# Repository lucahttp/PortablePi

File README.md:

# Portable Pi

Is a Father Board witch can connect to the raspberry pi (currently compatible to this gpio configuration, orange pi thinkercard, an anothers) this aport an Screen and keyboard (on one board) then i will add more things like audio jack, ethernet port, hub USB and everything you can imagine and put in your pockets.

render of prototype ver 8.8

## History
it started when i wanted to buy the newly released Pocket Chip (https://imgur.com/l437LvK 50 USD + taxes + shipping, something of 120 USD)the chip is a competitor of the raspberry pi but offered for 9 USD and for 40 USD more could you make this pocket.

everything looked like fine until the company that makes CHIP, declared bankrupt.

 # Search a compatible keyboard for the portable pi

 ## 1. Usb Bluetooth keyboard (cheaply)
 
the first option I thought (my father told me) was a bluetooth keyboard (is very cheaply opcion for those dont like the hardware) but i think isnt practical

 ## 2. Xbox ChatPad
 
the second opcion is a Xbox Chatpad but is missing keys like >< ,Ctrl , Alt, Command and others.
if you not need this keys is a good opcion for this project

the way to connect to the raspberry is a reprogram the Microchip PIC inside the keyboard, BenHacksShow show how do it [here](https://www.youtube.com/watch?v=Hjdj14C_jAI) and others examples [with raspberry](https://www.youtube.com/watch?v=2sVS-jMGD7w), [an brazilian](https://www.youtube.com/watch?v=Mo7BqMrNIDs) and [this](https://www.youtube.com/watch?v=I20lXAS_IJs)

it also can use directly like TX/RX but have to run aprogram to convert this signals in keyboard inputs and it slow down the limited resources of the computer. [here in reddit](https://www.reddit.com/r/raspberry_pi/comments/5t4xgy/raspberry_pi_xbox_chatpad_keyboard/)

 ## 3. Arduino Usb Keyboard or Serial 
 
the third opcion that came my way that i was found are a Arduino Pro Micro as a USB keyboard like [teensy Thumb Keyboard](https://hackaday.io/project/162281-teensy-thumb-keyboard) but in this opcion i would have to conect via USB to the raspberry and this is not a good idea because isnt practical

but i dont discard the idea of adapt this opcion for use via GPIO

- the teensy Thumb Keyboard
  [teensy Thumb Keyboard](https://hackaday.io/project/162281-teensy-thumb-keyboard) 

 - RC2014 keyboard
 
   The RC2014 [page](http://rc2014.co.uk/modules/universal-micro-keyboard/) shown a project but i dont have any idea of how to       
   adapt this to PortablePi

   [Uinput: The New Hope]()
 ## 4. Usb keyboard (very cheaply)
 
 This opcion is better for those do not have a way to get electronic components but the layout and matrix config is not prepared to direct access in the keyboard but could be config these features via software

 [design of cheaply USB Keyboard opcion](https://github.com/lukaneco/USB-keyboard-Board-PCB-pinout-diagram)

 ## 5. the way most factible is TCA8418

I found that they use the other projects like PocketChip or qwertyPi and others better keyboards for raspberry pi (and others microcomputers) more professionals. the problem is that component isnt easyly to found in my country and is a smaller than otrer solutions (hard to solder to the board).

a good news is that the documentation in the [manufacturer page](http://www.ti.com/product/TCA8418)

https://e2e.ti.com/support/interface/f/138/t/202938

[Datasheet of TCA8418](www.ti.com/lit/ds/symlink/tca8418.pdf)

[Code for malti](https://hackaday.io/project/5081-malti/log/17068-it-lives)

- [Malti](https://hackaday.io/project/5081-malti) is a similar project but that dont have the idea of easy plug and play.

- [qwertyPi](https://mozzwald.com/articles/2017/12/01/qwertypi-a-handheld-raspberry-pi-qwerty-computer) is the more similar  project but that dont have the easy plug of the raspberry 

- [Ben Heck’s DIY Calculator](https://www.youtube.com/watch?v=lJu1ij_Emlk) is a similar project for other destiny

- [other font of information]() that guy have an project to make this way (the page is writed in german)

  - [video](https://www.youtube.com/watch?v=j4ymw0hWN1o)
  
  - [web page](https://5volt-junkie.net/i2c-keypad/)
  
- [pwav robot](https://twitter.com/pwavrobot) is other guy that make something with TCA8418

  - [link](https://twitter.com/pwavrobot/status/1075758165944385536)

  - [snaponair](http://www.snaponair.com/)

  - [lorawan pager](https://hackaday.io/project/22038-the-lorawan-pager)

  - [zerophone](https://hackaday.io/project/19035-zerophone-a-raspberry-pi-smartphone)

repeat, the problem is the shipping from US or China is very expensive and it takes a long time to get here.
i found an options to buy in [Aliexpress](https://es.aliexpress.com/wholesale?catId=0&initiative_id=SB_20190210085412&SearchText=TCA8418) relatively cheap, Mouser, TI store and others sellers the shipping cost is more than aliexpress but more quickly (about 40 usd the shipping cost).

 ## 6. the way most cheaply and elaborate is PCF8574 with Python
 ### 12/03/19
I found this, previusly i had trouble undertand about the UINPUT python library for use with PCF8574
 http://blog.thestateofme.com/2012/08/10/raspberry-pi-gpio-joystick/

 # Search a display for the portable pi

 I'm still looking for better options for now i use the cheapest display quality/price, and that is 
 
- Pi Lcd 3.5 Touch 320x480
 [3.5inch RPi LCD 480x320](https://www.waveshare.com/3.5inch-rpi-lcd-a.htm)
 via GPIO (for female header, i will replaced with other connector smaller)

   the raspberry comunicate to the display via SPI, i dont think abaout others ways to gotcha it. 
   i know that the raspberry pi 2/3/other SBC have a DSI conector but i dont know how to use this

- via HDMI (i dont not recomend this opcion because it will discard the plug and plug metodology)

# Refresh frequency - display for the portable pi - update 03/03/19

 in the followind [video]( https://www.youtube.com/watch?v=SGMC0t33C50) show the problem abaout the latency of our display
 https://www.youtube.com/watch?v=SGMC0t33C50
 
 the framerate is very poor

 ## display driver customizing
 
 the other day i seen this [post]( https://github.com/juj/fbcp-ili9341), is a post abaout the driver configuration for increase the display quality but now i dont have the display for testing this code
 
 https://github.com/juj/fbcp-ili9341

## hyperpixel is a most powerfull solution but is very expensive and use more pins (all of pins xd)

https://www.adafruit.com/product/3932

## Another good display but it is also expensive
in the next [video](https://www.youtube.com/watch?v=9fgWt42FThU), i have seen the review of a display that to be the best display for gaming

https://www.youtube.com/watch?v=9fgWt42FThU

https://www.banggood.com/Geekwrom-HD-3_5-Inch-TFT-Display-Shield-800x480-For-Raspberry-Pi-3B-2B-Acrylic-Matching-Case-Kit-p-1096477.html?utm_source=Youtube&utm_medium=cussku&utm_campaign=10517404_1096477&utm_content=1087&cur_warehouse=CN

# Concept

the general idea is offer make portable the raspberry pi without discard the posibility of extract it, the purpose of this is debug projects anywhere without a desktop computer or notebook

https://imgur.com/8SMtQg4 

to make conceptual maps is a good tool [Cmap](https://cmapcloud.ihmc.us/)

# About Pocket Chip

is currently unavailable

https://www.pcworld.com/article/3094364/hardware/inside-the-pocketchip-a-49-portable-linux-computer.html

the page not found in the internet neither the documentation to make other similar

https://www.newmuseumstore.org/next-thing-co-pocket-chip

# Upgrade 09/02/2019
## investigating a new Keyboard IC - MSP430 is a very cheaply solution

i was surfing the red when appear savage news
i found an IC wich can use for the keyboard matrix and there yet was coding by usb and by I2C

http://www.ti.com/lit/ug/tidu521/tidu521.pdf

i will research abaout how to use this in the project

# Upgrade 11/02/2019
## investigating a new Keyboard software - Uinput is a very easy to use solution

i thinking about use uinput library of python, before dont considereded because CPU consumition but it would be minimal than the    
normal use, unless we care a lot about the performance issue would be a good option.

and matrix can be via atmega328 or some IC to do convert multiple inputs on less than, like pcf8574 or other I2C to parallel

http://www.ti.com/lit/ds/symlink/pcf8574.pdf

could also make atmega328 code to compatible for existing TCA8418 driver CODE or such any other similar

https://github.com/tuomasjjrasanen/python-uinput

https://pypi.org/project/python-uinput/

http://tjjr.fi/sw/python-uinput/

https://launchpad.net/python-uinput

this option is used for retro pi and other similar projects

# Upgrade 12/02/2019
## there is a thread in reddit of the chip 

there is a thread on reddit:
https://www.reddit.com/r/ChipCommunity/comments/amldpz/trying_to_recreate_a_pocketchip_with_a_raspberry/

# Update 17/02/2019
## meassurement pcf8574 in breadboard 

my raspberry pi zero does not have a strip of pins welded in the GPIO, I will buy a strip of male pins to put on the gpio to be able to take measurements

of course im going to have buy a pcf8574 in DIP format

# Update 01/03/2019
## meassurement pcf8574 in breadboard 

i bought a pcf8574 on module format, i got a LCD HD44780 LCD I2C controller for other purposes because i can get to use it for this project, the inconvinient is that one of the pins is used for the transistor of backlight (or i believe that).
the pin that is already used is P3. I bought this module and not the only IC because in my country is more cheaply :) and in the future i think going to desoldering the ic and soldering it in the final board

http://ict-bits.blogspot.com/2015/03/modding-lcd1602-i2ciic-adapter-board-to.html

https://www.instructables.com/id/Arduino-I2C-LCD-Driver-Library-and-PackMan/

https://github.com/Nilhcem/lcd-pcf8574-androidthings

<!--  --> 

# Update 03/03/19

searching a good display

[this is a better option for a cheap build](https://es.aliexpress.com/store/product/1pcs-3-2-inch-18P-SPI-TFT-LCD-Screen-without-Touch-panel-ILI9341-Drive-IC-240/133690_32819384322.html), have a good refresh frequency 

# Update 21/03/19 the last day of summer

too late, someone already make an opensource project more little and powerfull design

[video](https://www.youtube.com/watch?v=rN4tRiI-K5M)

[link](https://www.tindie.com/products/electronictrik/snaponair-raspberry-pi-zero-pcb/)

I will continue to develop it because these components are not available in my country :( macri intensifies

###########################################################################################################################
###########################################################################################################################
###########################################################################################################################

# Español

# Portable Pi

Es una "Placa Padre" la cual se conecta a la Raspberry (y compatible con otras placas) esta le brinda una pantalla y un teclado (en una sola placa) luego la voy a poner mas cosas como un jack de audio, un puerto ethernet, un hub usb y todo lo que puedas imaginar o poner en tus bolsillos.

 esta era una competidora de la raspberry pi pero de un

## History

todo comenzo cuando queria comprarme la Pocket Chip (https://imgur.com/l437LvK 65 USD +-, es una computadora portable basada en ARM), como vivo en argentina comprarla me iba a salir alrededor de 6000 ars o 150 USD por lo que preferi intentar construirme una parecida basada en la conocida raspberry Pi , no estoy seguro si en la Pi3 o Pi Zero por un tema de ergonomia en la mano y consumo energetico.

el diseño al estar basado en la pocket chip la raspberry pi seria insertada con sus GPIOs machos desde atras del PortablePi (todavia nose si esta al estar solamente sujeta con los gpios va a quedar bien agarrada, pero como la idea es que la raspberry sea de facil acceso para poder sacarla del "Expansion Board" y usarla como cualquier Raspberry pi)

## Compabilitys with Others Single Board Computers

Este diseño tambien se podria adaptar a las otras placas como a Orange Pi, Pine64, LattePanda , y otras placas, hasta las que no tiene salida de video ya que esta pantalla es via SPI.

seria tanto como hacer espacio en el diseño del PortablePi para que entre el conector para otra placa en caso de que no comparta la distribucion de pines con la raspberry 

//para ver los pines y sus valores dejo una pagina que te los muestra y explica que hace cada uno

https://pinout.xyz

## Compabilitys with Operatives Systems

el proyecto esta pensado para que funcione en una raspberry pi zero con raspbian o alguna distribucion que soporte tan poca RAM pero la verdad no conozco la forma de comunicar el display via SPI a otros sistemas operativos o a otras arquitecturas de procesadores ya que los drivers del fabricante solo estan pensados para la raspberry pi con raspbian o alguna distro parecida.

## Keyboard

El teclado de la Pocket pi inicialmente lo iba a hacer via USB reutilizando la placa logica de un teclado comun que sale alrededor de 2 USD o uno roto que podramos conseguir, pero me puse a pensar que no seria comodo para sacar la raspberry de y otros proyectos parecidos como la qwertyPi hacen uso del TC8418 pero esto es dificil de conseguir en donde me ubico, quizas lo podria conseguir via aliexpress que me saldria algo de 10 USD pero anda a saber cuando va a llegar 

hace varios años me compre la raspberry pi zero w por lo que actualmente el diseño esta pensado en esta pero en un futuro no muy lejano (si llego a conseguir una raspberry pi 3 o 2 del modelo B) pienso adaptarla a esta ya que posee 4 USB nativos, ethernet y un hdmi completo (un problema en esto es que pensaba poner la parte de los USB y el ethernet que sobresalga un poco por la parte superior pero si esta centrada en la parte superior el HDMI, Jack de video y el pin de carga quedan dentro del diseño y sin un facil acceso desde el costado del dispositivo por lo que una opcion seria poner esta en un costado, el izquierdo para tener el acceso a los puertos pero quedaria desentrado)

https://imgur.com/PwzQMJI

# Concept

https://imgur.com/8SMtQg4

https://cmapcloud.ihmc.us/

# About Pocket Chip

is currently unavailable
https://www.pcworld.com/article/3094364/hardware/inside-the-pocketchip-a-49-portable-linux-computer.html

https://www.newmuseumstore.org/next-thing-co-pocket-chip

# Upgrade 09/02/2019
## investigating a new Keyboard IC - MSP430 is a very cheaply solution

estaba boludeando por internet cuando noticia salvaje aparece xdxd
encontre que hay un IC que se puede usar para la matris del keyboard y que ya esta desarrollado el codigo y los drivers tanto por usb como por I2C

http://www.ti.com/lit/ug/tidu521/tidu521.pdf

# Upgrade 11/02/2019
## investigating a new Keyboard software - Uinput is a very easy to use solution

i thinking about use uinput library of python, before dont considereded because CPU consumition but it would be minimal than the    
normal use, unless we care a lot about the performance issue would be a good option.

and matrix can be via atmega328 or some IC to do convert multiple inputs on less than, like pcf8574 or other I2C to parallel

http://www.ti.com/lit/ds/symlink/pcf8574.pdf

could also make atmega328 code to compatible for existing TCA8418 driver CODE or such any other similar

https://github.com/tuomasjjrasanen/python-uinput

https://pypi.org/project/python-uinput/

http://tjjr.fi/sw/python-uinput/

https://launchpad.net/python-uinput

this option is used for retro pi and other similar projects

voy a investigar sobre como emplearlo en este proyecto

there is a thread on reddit:
https://www.reddit.com/r/ChipCommunity/comments/amldpz/trying_to_recreate_a_pocketchip_with_a_raspberry/

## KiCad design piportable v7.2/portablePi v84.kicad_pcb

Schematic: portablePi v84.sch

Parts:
C1, C2: C_Small; C_Axial_L5.1mm_D3.1mm_P7.50mm_Horizontal
D1, D2, D3, D4, D5, D6, D7, D8, D9, D10: 1N4148; D_T-1_P5.08mm_Horizontal
DS1: 3.5_Inch_RPI; 3.5 inch RPi LCD
IC1: Raspberry_Pi_Zero_W_(v1.3); RASPBERRY_PI_ZERO_W; Manufacturer_Part_Number Raspberry Pi Zero W (v1.3)
J1: AudioJack3; Jack_3.5mm_Ledino_KB3SPRS_Horizontal
SW0, SW1, SW2, SW3, SW4, SW5, SW6, SW7, SW8, SW9, SW10, SW11, SW12, SW13, SW14, SW15, SW16, SW17, SW18, SW19, SW20, SW21, SW22, SW23, SW24, SW25, SW26, SW27, SW28, SW29, SW30, SW31, SW32, SW33, SW34, SW35, SW36, SW37, SW38, SW39, SW40, SW41, SW42, SW43, SW44, SW45, SW46, SW47, SW48, SW49, SW50, SW51, SW52, SW53, SW54, SW55, SW56: SW_Push; SW_PUSH_6mm
U1: ATmega328P-PU; DIP-28_W7.62mm
U2, U3: PCF8574; DIP-16_W10.16mm_LongPads
Y1: Crystal; Crystal_HC18-U_Vertical

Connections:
+3V3: DS1.1, DS1.17, IC1.1 (+3.3V_1), IC1.17 (+3.3V_2)
+5V: DS1.2, DS1.4, IC1.2 (+5V_1), IC1.4 (+5V_2), U1.7 (VCC), U1.20 (AVCC), U1.21 (AREF), U2.16 (VDD), U3.16 (VDD)
Col0: SW40.1, SW41.1, SW43.1, SW44.1, SW45.1, SW46.1, SW47.1, SW48.1, SW49.1, U1.18 (PB4), U2.9 (P4)
Col1: SW42.1, SW50.1, SW51.1, SW52.1, SW53.1, SW54.1, SW55.1, SW56.1, U1.19 (PB5), U2.10 (P5)
Col2: SW0.1, SW1.1, SW2.1, SW3.1, SW4.1, SW5.1, SW6.1, SW7.1, SW8.1, SW9.1, U1.17 (PB3), U2.7 (P3)
Col3: SW10.1, SW11.1, SW12.1, SW13.1, SW14.1, SW15.1, SW16.1, SW17.1, SW18.1, SW19.1, U1.16 (PB2), U2.6 (P2)
Col4: SW20.1, SW21.1, SW22.1, SW23.1, SW24.1, SW25.1, SW26.1, SW27.1, SW28.1, SW29.1, U1.15 (PB1), U2.5 (P1)
Col5: SW30.1, SW31.1, SW32.1, SW33.1, SW34.1, SW35.1, SW36.1, SW37.1, SW38.1, U1.14 (PB0), U2.4 (P0)
GND: C1.2, C2.1, DS1.6, DS1.9, DS1.14, DS1.20, DS1.25, IC1.6 (GND_1), IC1.9 (GND_2), IC1.14 (GND_3), IC1.20 (GND_4), IC1.25 (GND_5), U1.8 (GND), U1.22 (GND), U2.8 (VSS), U3.8 (VSS)
LCD_CS: DS1.24, IC1.24 (GPIO_8/SPI0_CE1_N)
LCD_RS: DS1.18, IC1.18 (GPIO_24)
LCD_SCK: DS1.23, IC1.23 (GPIO_11/SPI0_SCLK)
unnamed: D1.2 (A), SW0.2, SW10.2, SW20.2, SW40.2, SW42.2
unnamed: D2.2 (A), SW1.2, SW11.2, SW21.2, SW30.2, SW41.2
unnamed: D3.2 (A), SW2.2, SW12.2, SW22.2, SW31.2, SW43.2, SW50.2
unnamed: D4.2 (A), SW3.2, SW13.2, SW23.2, SW32.2, SW44.2, SW51.2
unnamed: D5.2 (A), SW4.2, SW14.2, SW24.2, SW33.2, SW45.2, SW52.2
unnamed: D6.2 (A), SW5.2, SW15.2, SW25.2, SW34.2, SW46.2, SW53.2
unnamed: D7.2 (A), SW6.2, SW16.2, SW26.2, SW35.2, SW47.2, SW54.2
unnamed: D8.2 (A), SW7.2, SW17.2, SW27.2, SW36.2, SW48.2, SW55.2
unnamed: D9.2 (A), SW8.2, SW18.2, SW28.2, SW37.2, SW39.1, SW49.2, SW56.2
unnamed: D10.2 (A), SW9.2, SW19.2, SW29.2, SW38.2, SW39.2
unnamed: IC1.3 (GPIO_2/[I2C]_SDA), U2.15 (SDA), U3.15 (SDA)
unnamed: IC1.5 (GPIO_3/[I2C]_SCL), U2.14 (SCL), U3.14 (SCL)
Osc1: C2.2, U1.9 (XTAL1/PB6), Y1.2
Osc2: C1.1, U1.10 (XTAL2/PB7), Y1.1
RST: DS1.22, IC1.22 (GPIO_25)
Reset: U1.1 (~RESET~/PC6)
Row0: D1.1 (K), U1.23 (PC0), U2.11 (P6)
Row1: D2.1 (K), U1.24 (PC1), U2.12 (P7)
Row2: D3.1 (K), U1.25 (PC2), U3.4 (P0)
Row3: D4.1 (K), U1.26 (PC3), U3.5 (P1)
Row4: D5.1 (K), U1.27 (PC4), U3.6 (P2)
Row5: D6.1 (K), U1.28 (PC5), U3.7 (P3)
Row6: D7.1 (K), U1.6 (PD4), U3.9 (P4)
Row7: D8.1 (K), U1.11 (PD5), U3.10 (P5)
Row8: D9.1 (K), U1.12 (PD6), U3.11 (P6)
Row9: D10.1 (K), U1.13 (PD7), U3.12 (P7)
Serial_RX: U1.2 (PD0)
Serial_TX: U1.3 (PD1)
TP_CS: DS1.26, IC1.26 (GPIO_7/SPI0_CE2_N)
TP_IRQ: DS1.11, IC1.11 (GPIO_17/SPI1_CS1)
TP_SO: DS1.21, IC1.21 (GPIO_9/SPI0_MISO)
USB_D+: U1.4 (PD2)
USB_D-: U1.5 (PD3)

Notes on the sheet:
Opcional USB

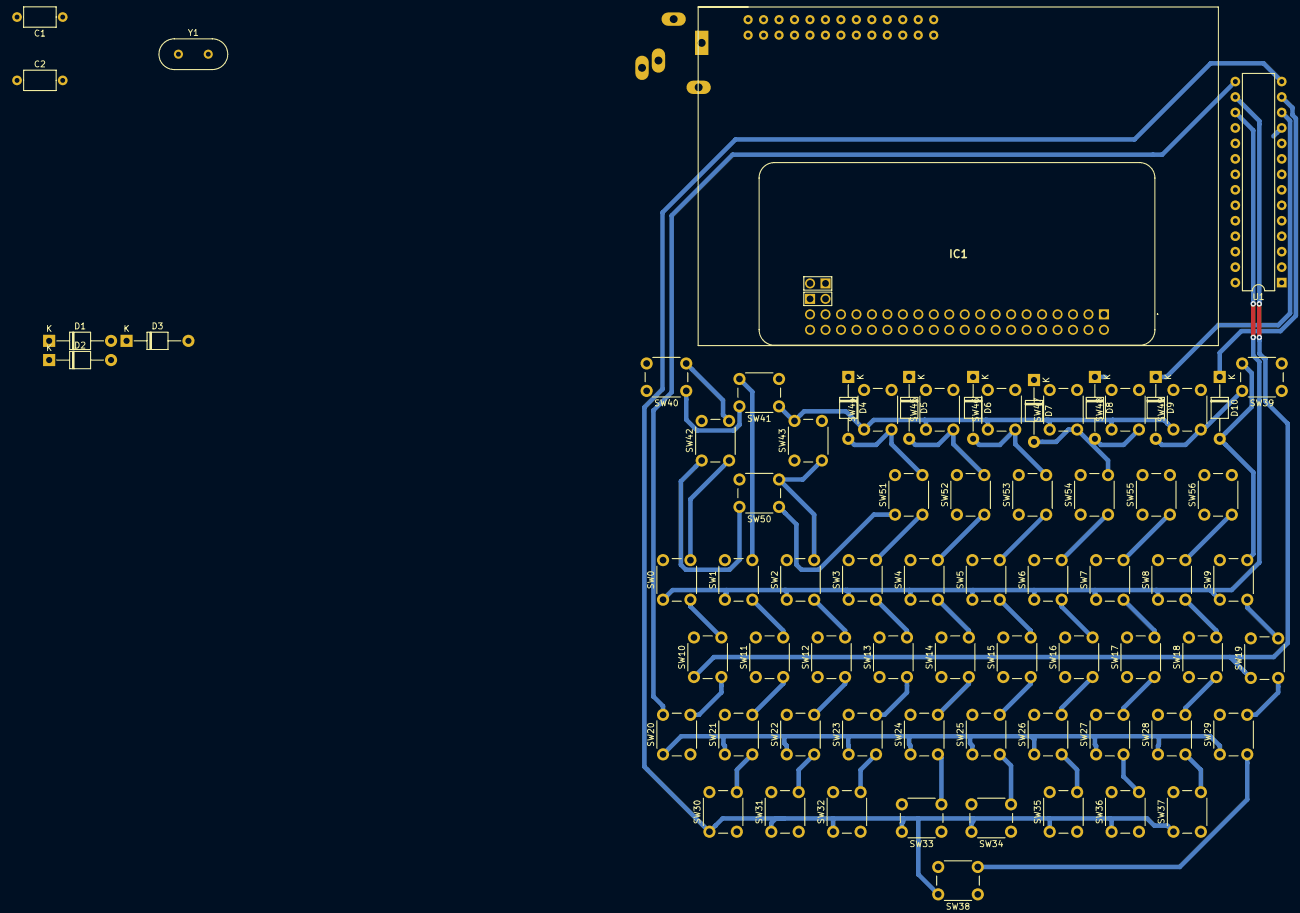
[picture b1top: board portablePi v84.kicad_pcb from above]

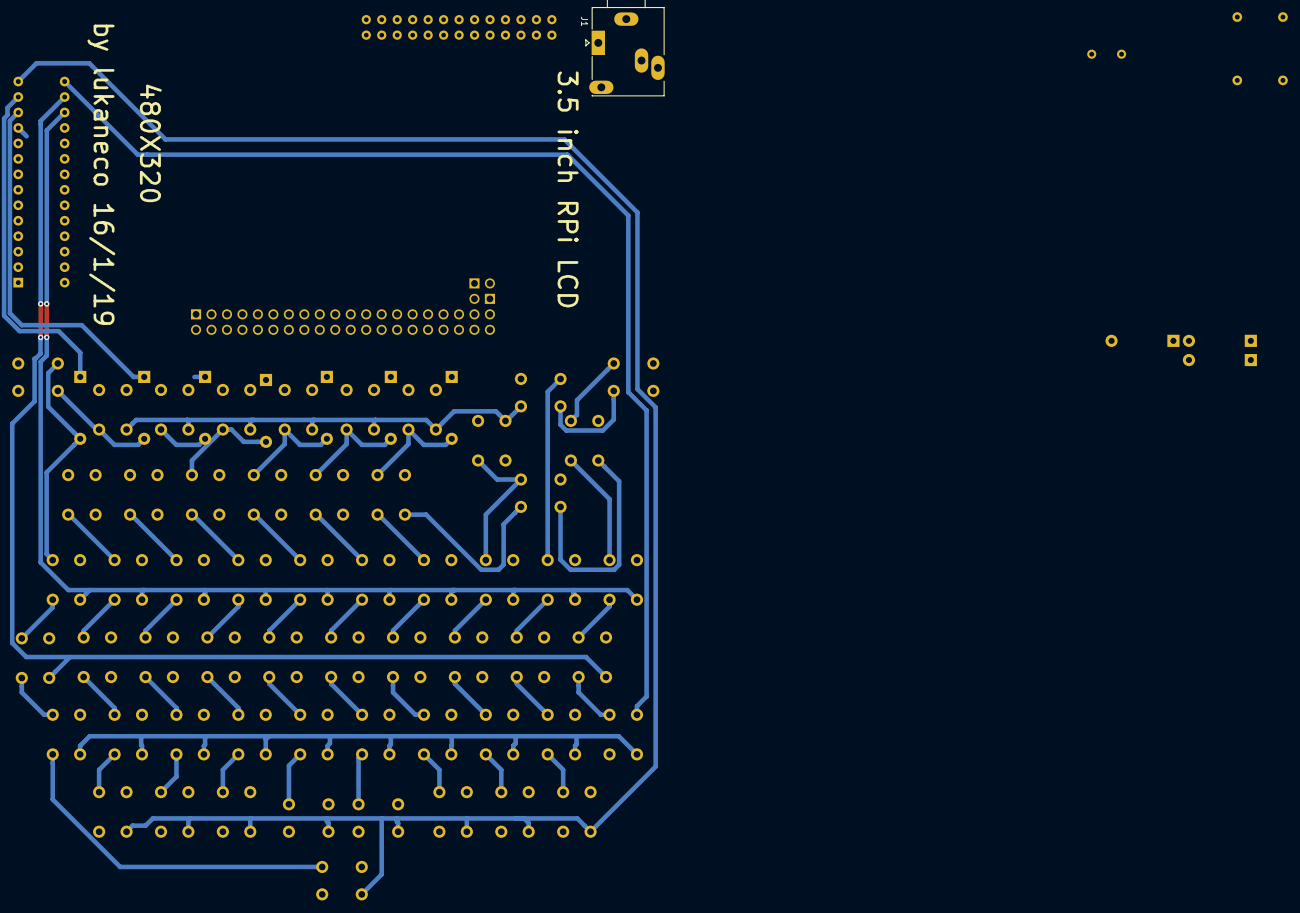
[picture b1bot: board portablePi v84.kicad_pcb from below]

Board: 2 copper layers, 74 parts (2 on the bottom side), 38 nets.

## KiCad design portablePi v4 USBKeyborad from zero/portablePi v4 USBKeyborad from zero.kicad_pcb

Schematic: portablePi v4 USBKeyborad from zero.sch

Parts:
DS1: 3.5_Inch_RPI; 3.5 inch RPi LCD
IC1: Raspberry_Pi_Zero_W_(v1.3); RASPBERRY_PI_ZERO_W; Manufacturer_Part_Number Raspberry Pi Zero W (v1.3)
J1: AudioJack3; Jack_3.5mm_Ledino_KB3SPRS_Horizontal
SW0, SW1, SW2, SW3, SW4, SW5, SW6, SW7, SW8, SW9, SW10, SW11, SW12, SW13, SW14, SW15, SW16, SW17, SW18, SW19, SW20, SW21, SW22, SW23, SW24, SW25, SW26, SW27, SW28, SW29, SW30, SW31, SW32, SW33, SW34, SW35, SW36, SW37, SW38, SW39, SW40, SW41, SW42, SW43, SW44, SW45, SW46, SW47, SW48, SW49, SW50, SW51, SW52, SW53, SW54, SW55, SW56: SW_Push; SW_PUSH_6mm
U1: ATmega328P-PU; DIP-28_W7.62mm

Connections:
Col0: SW40.1, SW41.1, SW42.1, SW43.1, SW44.1, SW45.1, SW46.1, SW47.1, SW48.1, SW49.1
Col1: SW50.1, SW51.1, SW52.1, SW53.1, SW54.1, SW55.1, SW56.1
Col2: SW0.1, SW1.1, SW2.1, SW3.1, SW4.1, SW5.1, SW6.1, SW7.1, SW8.1, SW9.1
Col3: SW10.1, SW11.1, SW12.1, SW13.1, SW14.1, SW15.1, SW16.1, SW17.1, SW18.1, SW19.1
Col4: SW20.1, SW21.1, SW22.1, SW23.1, SW24.1, SW25.1, SW26.1, SW27.1, SW28.1, SW29.1
Col5: SW30.1, SW31.1, SW32.1, SW33.1, SW34.1, SW35.1, SW36.1, SW37.1, SW38.1, SW39.1
unnamed: IC1.1 (+3.3V_1), IC1.17 (+3.3V_2)
unnamed: IC1.2 (+5V_1), IC1.4 (+5V_2)
unnamed: IC1.6 (GND_1), IC1.9 (GND_2), IC1.14 (GND_3), IC1.20 (GND_4), IC1.25 (GND_5)
unnamed: U1.8 (GND), U1.22 (GND)
Osc1: U1.9 (XTAL1/PB6)
Osc2: U1.10 (XTAL2/PB7)
Reset: U1.1 (~RESET~/PC6)
Serial_RX: U1.2 (PD0)
Serial_TX: U1.3 (PD1)
USB_D+: U1.4 (PD2)
USB_D-: U1.5 (PD3)

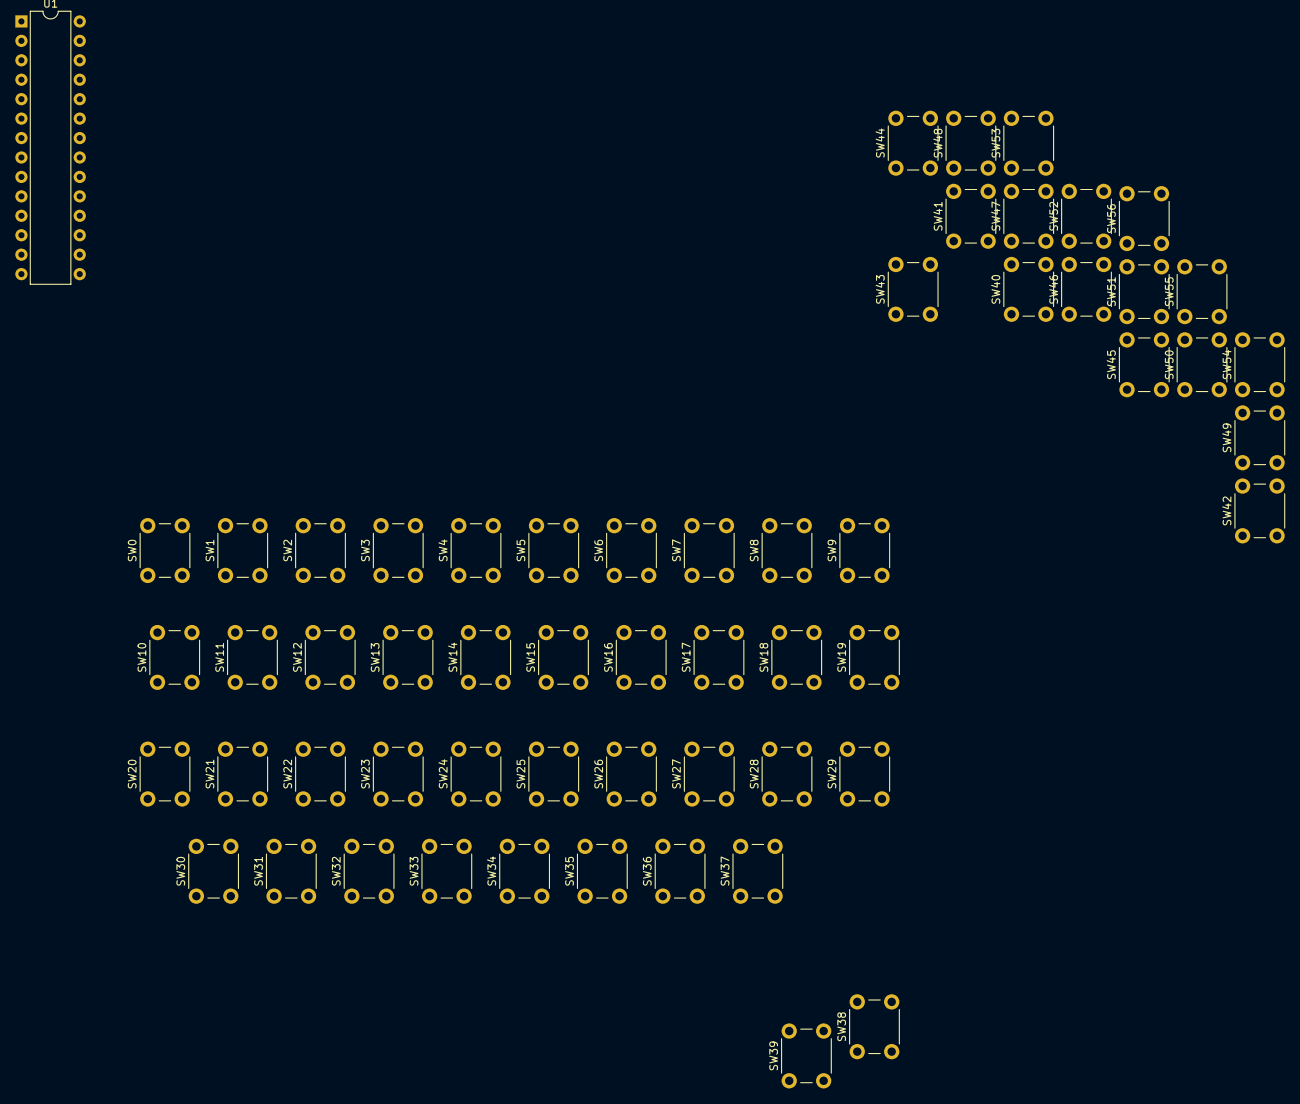
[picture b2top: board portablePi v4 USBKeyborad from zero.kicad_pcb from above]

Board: 2 copper layers, 58 parts (0 on the bottom side), 7 nets, no tracks yet.

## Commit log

2019-02-09 nothing new
2019-02-09 Only put a description
2019-02-09 nothing new is only a testing of a readme
2019-02-10 english update
2019-02-10 updating documentation
2019-02-10 update number twenty four xdxdxd
2019-02-10 quiero terminar ahhhhhhhhhhhhhhh
2019-02-10 add images
2019-02-10 updateimges
2019-02-11 updated of monday
2019-02-11 update now xdxd
2019-02-14 gggg
    gggg
2019-02-17 por estudiar
2019-02-17 orthography corrections
2019-03-01 actualiseishon
    gg
2019-03-21 sadness music
2019-03-21 the last versions
